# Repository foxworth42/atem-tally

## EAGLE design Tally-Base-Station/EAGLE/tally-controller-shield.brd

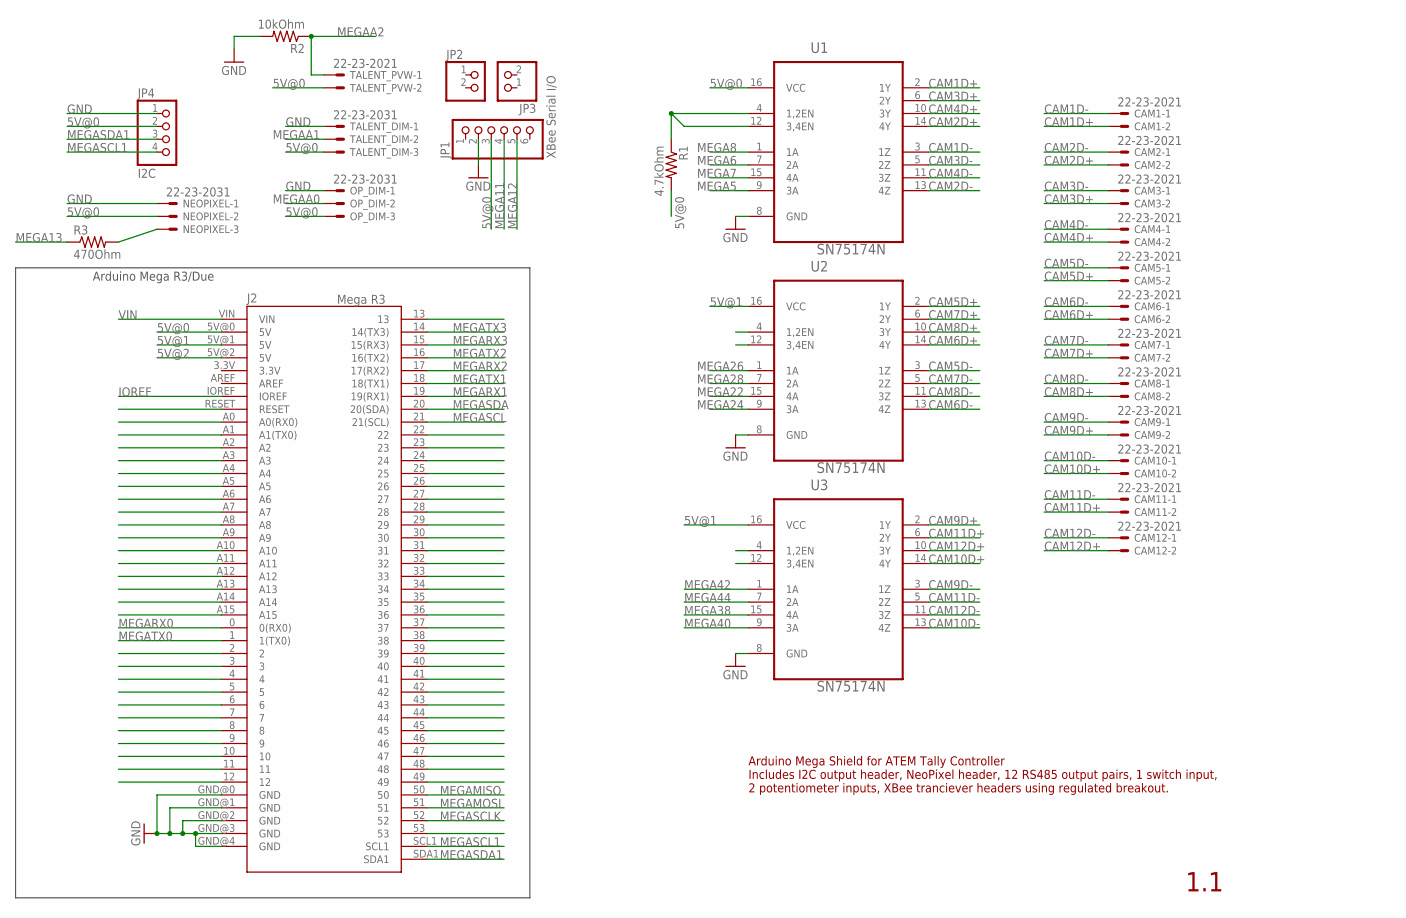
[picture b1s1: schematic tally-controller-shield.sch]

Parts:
CAM1, CAM2, CAM3, CAM4, CAM5, CAM6, CAM7, CAM8, CAM9, CAM10, CAM11, CAM12: 22-23-2021
J2: Mega R3; ARDUINO_MEGA
JP1: XBee Serial I/O; 1X06
JP2, JP3: PINHD-1X2; 1X02
JP4: I2C; 1X04
NEOPIXEL: 22-23-2031
OP_DIM: 22-23-2031
R1: 4.7kOhm; 0207/10
R2: 10kOhm; 0207/10
R3: 470Ohm; 0207/10
TALENT_DIM: 22-23-2031
TALENT_PVW: 22-23-2021
U1, U2, U3: SN75174N; DIP254P762X508-16

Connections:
5V@0: J2.5V@0 (5V), JP1.3, JP4.2, NEOPIXEL.2, OP_DIM.3, R1.2, TALENT_DIM.3, TALENT_PVW.2, U1.16 (VCC)
5V@1: J2.5V@1 (5V), U2.16 (VCC), U3.16 (VCC)
5V@2: J2.5V@2 (5V)
CAM1D+: CAM1.2, U1.2 (1Y)
CAM1D-: CAM1.1, U1.3 (1Z)
CAM2D+: CAM2.2, U1.14 (4Y)
CAM2D-: CAM2.1, U1.13 (4Z)
CAM3D+: CAM3.2, U1.6 (2Y)
CAM3D-: CAM3.1, U1.5 (2Z)
CAM4D+: CAM4.2, U1.10 (3Y)
CAM4D-: CAM4.1, U1.11 (3Z)
CAM5D+: CAM5.2, U2.2 (1Y)
CAM5D-: CAM5.1, U2.3 (1Z)
CAM6D+: CAM6.2, U2.14 (4Y)
CAM6D-: CAM6.1, U2.13 (4Z)
CAM7D+: CAM7.2, U2.6 (2Y)
CAM7D-: CAM7.1, U2.5 (2Z)
CAM8D+: CAM8.2, U2.10 (3Y)
CAM8D-: CAM8.1, U2.11 (3Z)
CAM9D+: CAM9.2, U3.2 (1Y)
CAM9D-: CAM9.1, U3.3 (1Z)
CAM10D+: CAM10.2, U3.14 (4Y)
CAM10D-: CAM10.1, U3.13 (4Z)
CAM11D+: CAM11.2, U3.6 (2Y)
CAM11D-: CAM11.1, U3.5 (2Z)
CAM12D+: CAM12.2, U3.10 (3Y)
CAM12D-: CAM12.1, U3.11 (3Z)
GND: J2.GND@0 (GND), J2.GND@1 (GND), J2.GND@2 (GND), J2.GND@3 (GND), J2.GND@4 (GND), JP1.2, JP4.1, NEOPIXEL.1, OP_DIM.1, R2.2, TALENT_DIM.1, U1.8 (GND), U2.8 (GND), U3.8 (GND)
IOREF: J2.IOREF
MEGA2: J2.2
MEGA3: J2.3
MEGA4: J2.4
MEGA5: J2.5, U1.9 (3A)
MEGA6: J2.6, U1.7 (2A)
MEGA7: J2.7, U1.15 (4A)
MEGA8: J2.8, U1.1 (1A)
MEGA9: J2.9
MEGA10: J2.10
MEGA11: J2.11, JP1.4
MEGA12: J2.12, JP1.5
MEGA13: J2.13, R3.1
MEGA22: J2.22, U2.15 (4A)
MEGA23: J2.23
MEGA24: J2.24, U2.9 (3A)
MEGA25: J2.25
MEGA26: J2.26, U2.1 (1A)
MEGA27: J2.27
MEGA28: J2.28, U2.7 (2A)
MEGA29: J2.29
MEGA30: J2.30
MEGA31: J2.31
MEGA32: J2.32
MEGA33: J2.33
MEGA34: J2.34
MEGA35: J2.35
MEGA36: J2.36
MEGA37: J2.37
MEGA38: J2.38, U3.15 (4A)
MEGA39: J2.39
MEGA40: J2.40, U3.9 (3A)
MEGA41: J2.41
MEGA42: J2.42, U3.1 (1A)
MEGA43: J2.43
MEGA44: J2.44, U3.7 (2A)
MEGA45: J2.45
MEGA46: J2.46
MEGA47: J2.47
MEGA48: J2.48
MEGA49: J2.49
MEGA53: J2.53
MEGAA0: J2.A0 (A0(RX0)), OP_DIM.2
MEGAA1: J2.A1 (A1(TX0)), TALENT_DIM.2
MEGAA2: J2.A2, R2.1, TALENT_PVW.1
MEGAA3: J2.A3
MEGAA4: J2.A4
MEGAA5: J2.A5
MEGAA6: J2.A6
MEGAA7: J2.A7
MEGAA8: J2.A8
MEGAA9: J2.A9
MEGAA10: J2.A10
MEGAA11: J2.A11
MEGAA12: J2.A12
MEGAA13: J2.A13
MEGAA14: J2.A14
MEGAA15: J2.A15
MEGAMISO: J2.50
MEGAMOSI: J2.51
MEGARX0: J2.0 (0(RX0))
MEGARX1: J2.19 (19(RX1))
MEGARX2: J2.17 (17(RX2))
MEGARX3: J2.15 (15(RX3))
MEGASCL: J2.21 (21(SCL))
MEGASCL1: J2.SCL1, JP4.4
MEGASCLK: J2.52
MEGASDA: J2.20 (20(SDA))
MEGASDA1: J2.SDA1, JP4.3
MEGATX0: J2.1 (1(TX0))
MEGATX1: J2.18 (18(TX1))
MEGATX2: J2.16 (16(TX2))
MEGATX3: J2.14 (14(TX3))
NEOPIXELDATA: NEOPIXEL.3, R3.2
RESET: J2.RESET
RS485EN: R1.1, U1.4 (1,2EN), U1.12 (3,4EN), U2.4 (1,2EN), U2.12 (3,4EN), U3.4 (1,2EN), U3.12 (3,4EN)
VIN: J2.VIN

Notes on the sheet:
Arduino Mega R3/Due
Arduino Mega Shield for ATEM Tally Controller Includes I2C output header, NeoPixel header, 12 RS485 output pairs, 1 switch input, 2 potentiometer inputs, XBee tranciever headers using regulated breakout.
1.1

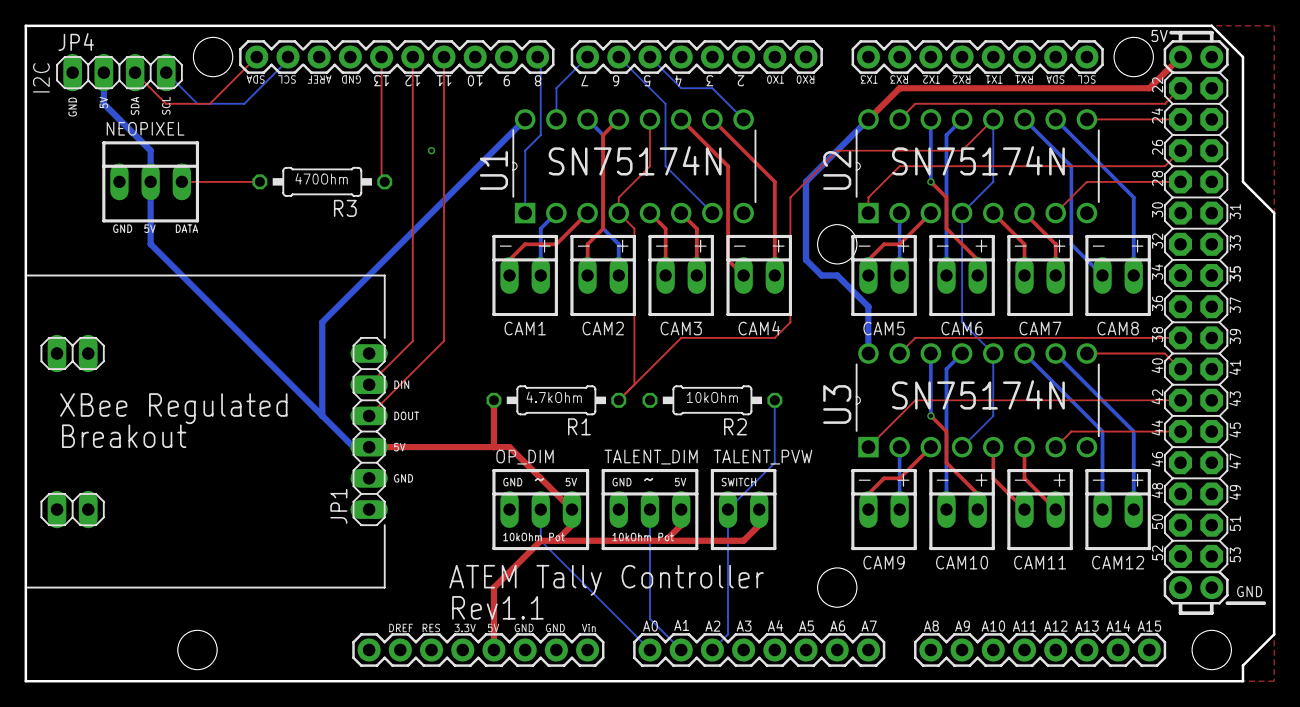
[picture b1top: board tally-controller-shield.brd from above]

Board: 2 copper layers, 101.6 x 53.3 mm, 27 parts (0 on the bottom side), 49 nets.

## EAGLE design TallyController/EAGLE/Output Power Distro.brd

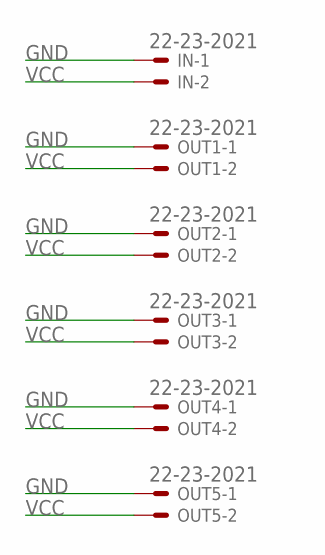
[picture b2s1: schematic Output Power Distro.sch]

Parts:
IN: 22-23-2021
OUT1, OUT2, OUT3, OUT4, OUT5: 22-23-2021

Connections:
GND: IN.1, OUT1.1, OUT2.1, OUT3.1, OUT4.1, OUT5.1
VCC: IN.2, OUT1.2, OUT2.2, OUT3.2, OUT4.2, OUT5.2

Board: 2 copper layers, 6 parts (0 on the bottom side), 2 nets, no tracks yet.
